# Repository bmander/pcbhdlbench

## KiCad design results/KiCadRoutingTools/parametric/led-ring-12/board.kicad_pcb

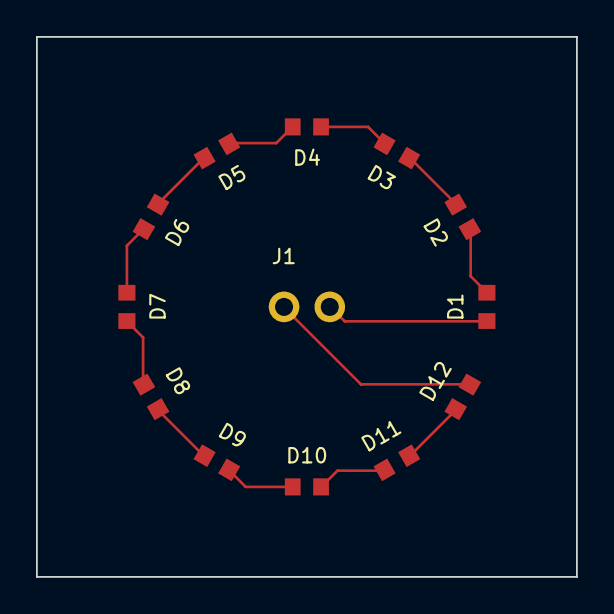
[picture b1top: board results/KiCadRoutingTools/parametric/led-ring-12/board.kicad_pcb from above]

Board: 2 copper layers, 30.0 x 30.0 mm, 13 parts (0 on the bottom side), 13 nets.

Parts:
D1, D2, D3, D4, D5, D6, D7, D8, D9, D10, D11, D12: LED_0603
J1: HDR_1x2_2.54

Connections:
GND: D1.K, J1.2
L1: D1.A, D2.K
L2: D2.A, D3.K
L3: D3.A, D4.K
L4: D4.A, D5.K
L5: D5.A, D6.K
L6: D6.A, D7.K
L7: D7.A, D8.K
L8: D8.A, D9.K
L9: D9.A, D10.K
L10: D10.A, D11.K
L11: D11.A, D12.K
VIN: D12.A, J1.1

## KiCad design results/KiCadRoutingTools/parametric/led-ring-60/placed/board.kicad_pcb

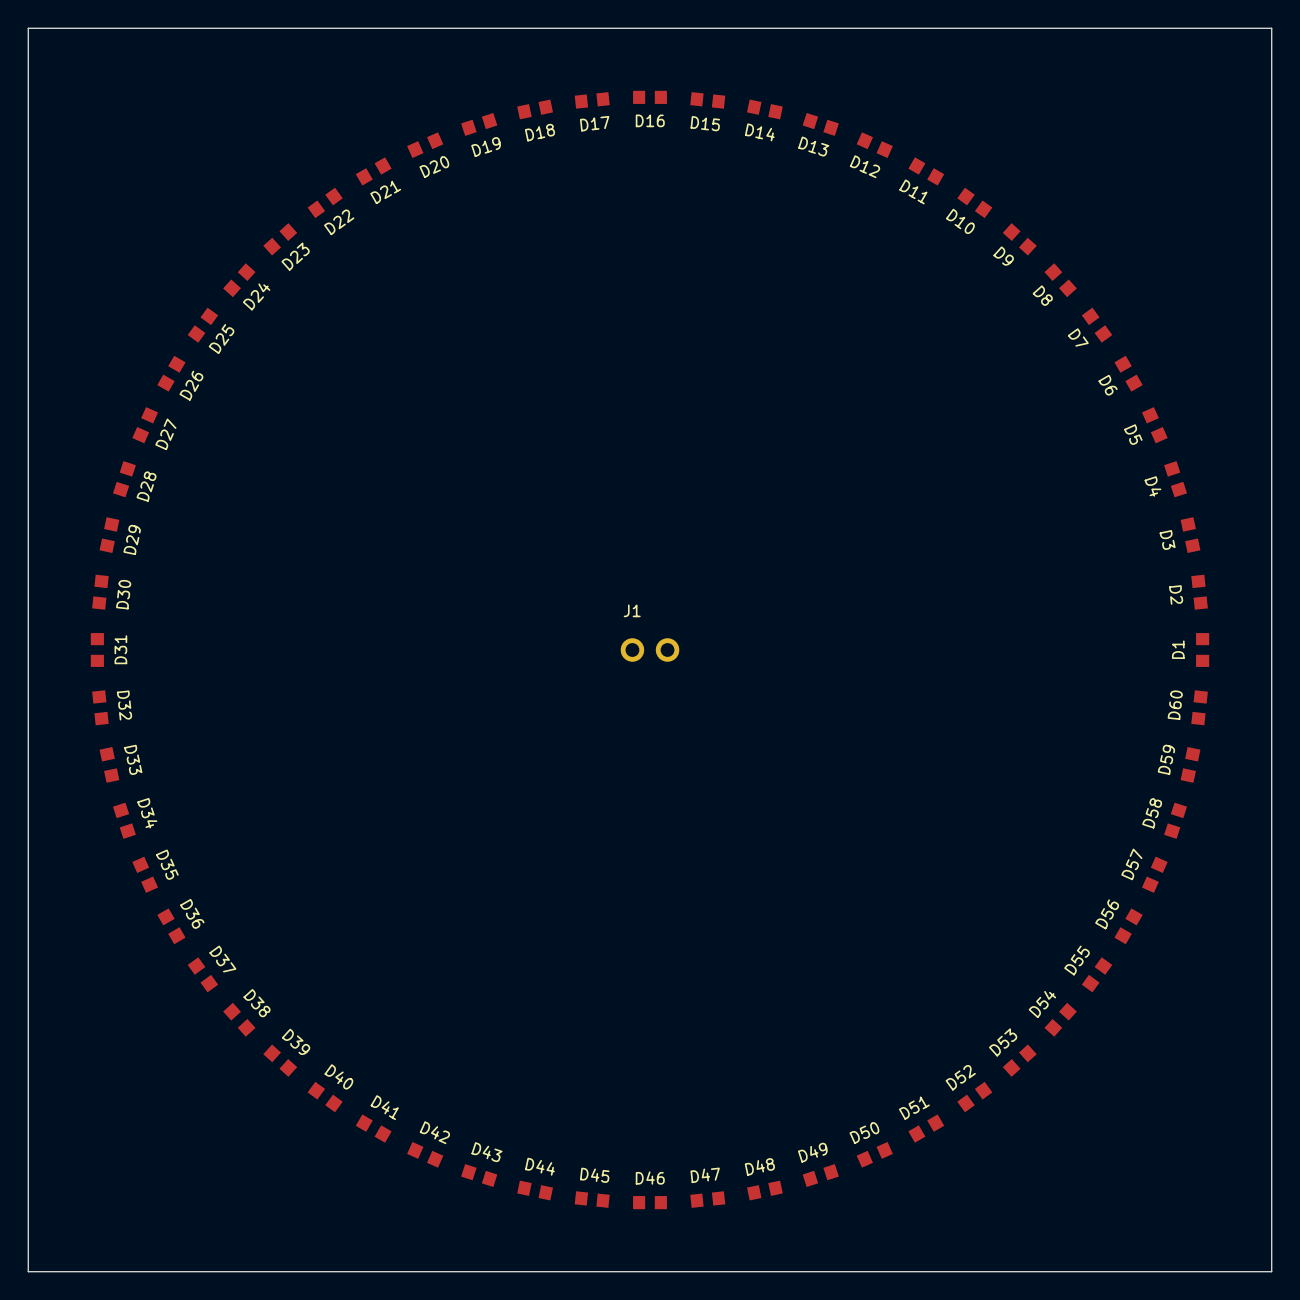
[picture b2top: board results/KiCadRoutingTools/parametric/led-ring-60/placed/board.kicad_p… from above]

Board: 2 copper layers, 90.0 x 90.0 mm, 61 parts (0 on the bottom side), 61 nets, no tracks yet.

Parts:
D1, D2, D3, D4, D5, D6, D7, D8, D9, D10, D11, D12, D13, D14, D15, D16, D17, D18, D19, D20, D21, D22, D23, D24, D25, D26, D27, D28, D29, D30, D31, D32, D33, D34, D35, D36, D37, D38, D39, D40, D41, D42, D43, D44, D45, D46, D47, D48, D49, D50, D51, D52, D53, D54, D55, D56, D57, D58, D59, D60: LED_0603
J1: HDR_1x2_2.54

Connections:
GND: D1.K, J1.2
L1: D1.A, D2.K
L2: D2.A, D3.K
L3: D3.A, D4.K
L4: D4.A, D5.K
L5: D5.A, D6.K
L6: D6.A, D7.K
L7: D7.A, D8.K
L8: D8.A, D9.K
L9: D9.A, D10.K
L10: D10.A, D11.K
L11: D11.A, D12.K
L12: D12.A, D13.K
L13: D13.A, D14.K
L14: D14.A, D15.K
L15: D15.A, D16.K
L16: D16.A, D17.K
L17: D17.A, D18.K
L18: D18.A, D19.K
L19: D19.A, D20.K
L20: D20.A, D21.K
L21: D21.A, D22.K
L22: D22.A, D23.K
L23: D23.A, D24.K
L24: D24.A, D25.K
L25: D25.A, D26.K
L26: D26.A, D27.K
L27: D27.A, D28.K
L28: D28.A, D29.K
L29: D29.A, D30.K
L30: D30.A, D31.K
L31: D31.A, D32.K
L32: D32.A, D33.K
L33: D33.A, D34.K
L34: D34.A, D35.K
L35: D35.A, D36.K
L36: D36.A, D37.K
L37: D37.A, D38.K
L38: D38.A, D39.K
L39: D39.A, D40.K
L40: D40.A, D41.K
L41: D41.A, D42.K
L42: D42.A, D43.K
L43: D43.A, D44.K
L44: D44.A, D45.K
L45: D45.A, D46.K
L46: D46.A, D47.K
L47: D47.A, D48.K
L48: D48.A, D49.K
L49: D49.A, D50.K
L50: D50.A, D51.K
L51: D51.A, D52.K
L52: D52.A, D53.K
L53: D53.A, D54.K
L54: D54.A, D55.K
L55: D55.A, D56.K
L56: D56.A, D57.K
L57: D57.A, D58.K
L58: D58.A, D59.K
L59: D59.A, D60.K
VIN: D60.A, J1.1

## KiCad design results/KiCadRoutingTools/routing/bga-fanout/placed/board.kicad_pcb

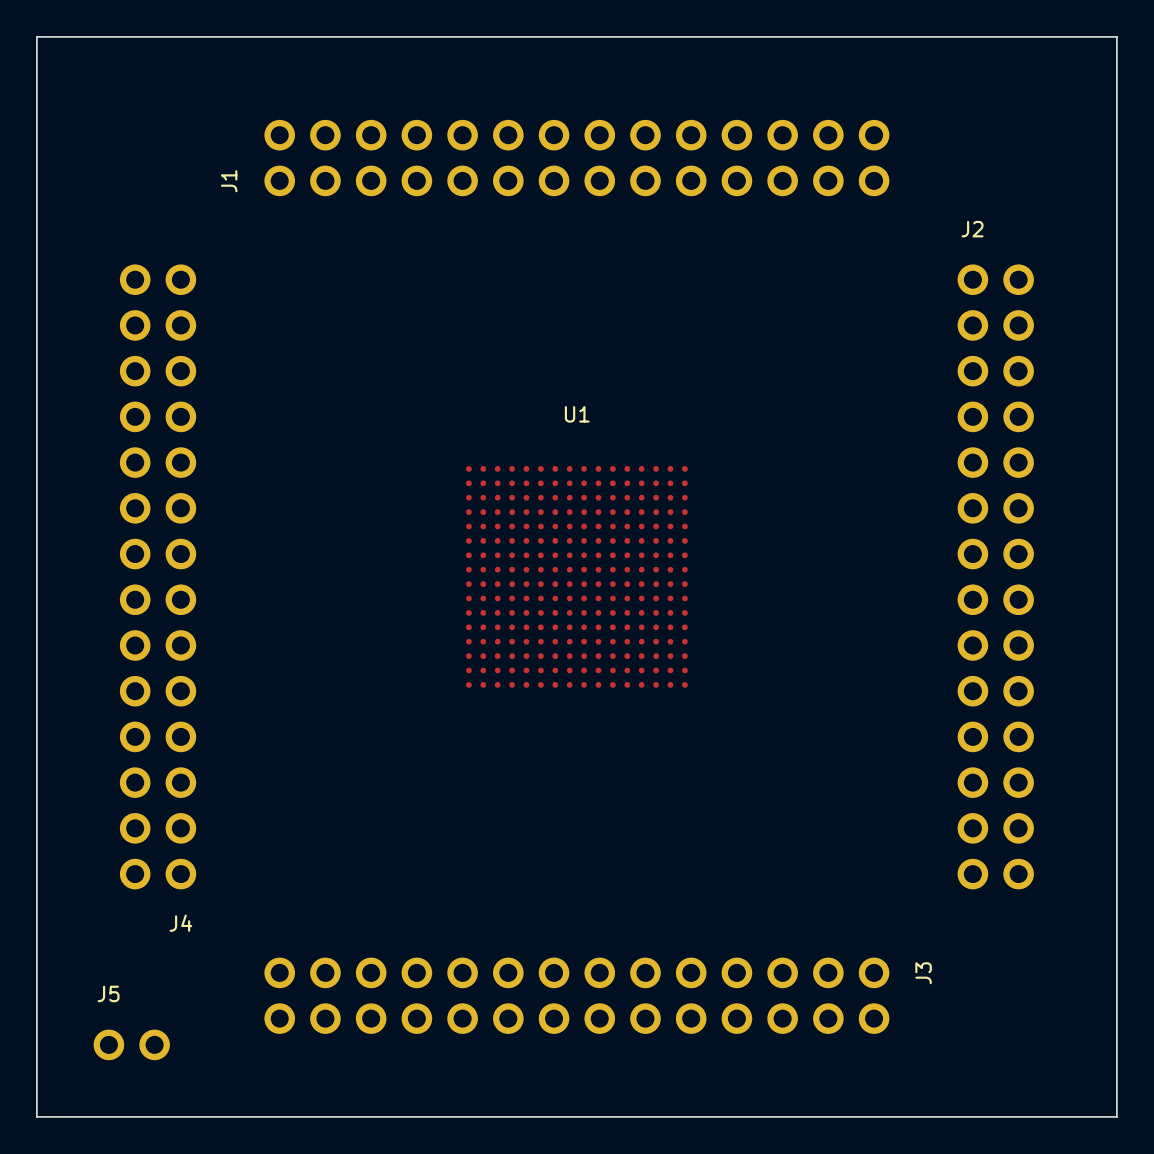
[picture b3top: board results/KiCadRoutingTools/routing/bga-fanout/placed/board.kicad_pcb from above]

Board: 4 copper layers, 60.0 x 60.0 mm, 6 parts (0 on the bottom side), 114 nets, no tracks yet.

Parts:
J1, J2, J3, J4: HDR_2x14_2.54
J5: HDR_1x2_2.54
U1: BGA-256

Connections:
A1: J1.1, U1.A1
A2: J1.2, U1.A2
A3: J1.4, U1.A3
A4: J1.6, U1.A4
A5: J1.8, U1.A5
A6: J1.10, U1.A6
A7: J1.12, U1.A7
A8: J1.14, U1.A8
A9: J1.16, U1.A9
A10: J1.18, U1.A10
A11: J1.20, U1.A11
A12: J1.22, U1.A12
A13: J1.24, U1.A13
A14: J1.26, U1.A14
A15: J1.28, U1.A15
A16: J2.1, U1.A16
B1: J4.28, U1.B1
B2: J1.3, U1.B2
B3: J1.5, U1.B3
B4: J1.7, U1.B4
B5: J1.9, U1.B5
B6: J1.11, U1.B6
B7: J1.13, U1.B7
B8: J1.15, U1.B8
B9: J1.17, U1.B9
B10: J1.19, U1.B10
B11: J1.21, U1.B11
B12: J1.23, U1.B12
B13: J1.25, U1.B13
B14: J1.27, U1.B14
B15: J2.3, U1.B15
B16: J2.2, U1.B16
C1: J4.26, U1.C1
C2: J4.27, U1.C2
C15: J2.5, U1.C15
C16: J2.4, U1.C16
D1: J4.24, U1.D1
D2: J4.25, U1.D2
D15: J2.7, U1.D15
D16: J2.6, U1.D16
E1: J4.22, U1.E1
E2: J4.23, U1.E2
E15: J2.9, U1.E15
E16: J2.8, U1.E16
F1: J4.20, U1.F1
F2: J4.21, U1.F2
F15: J2.11, U1.F15
F16: J2.10, U1.F16
G1: J4.18, U1.G1
G2: J4.19, U1.G2
G15: J2.13, U1.G15
G16: J2.12, U1.G16
GND: J5.2, U1.C3, U1.C5, U1.C7, U1.C9, U1.C11, U1.C13, U1.D4, U1.D6, U1.D8, U1.D10, U1.D12, U1.D14, U1.E3, U1.E5, U1.E7, U1.E9, U1.E11, U1.E13, U1.F4, U1.F6, U1.F8, U1.F10, U1.F12, U1.F14, U1.G3, U1.G5, U1.G7, U1.G9, U1.G11, U1.G13, U1.H4, U1.H6, U1.H8, U1.H10, U1.H12, U1.H14, U1.J3, U1.J5, U1.J7, U1.J9, U1.J11, U1.J13, U1.K4, U1.K6, U1.K8, U1.K10, U1.K12, U1.K14, U1.L3, U1.L5, U1.L7, U1.L9, U1.L11, U1.L13, U1.M4, U1.M6, U1.M8, U1.M10, U1.M12, U1.M14, U1.N3, U1.N5, U1.N7, U1.N9, U1.N11, U1.N13, U1.P4, U1.P6, U1.P8, U1.P10, U1.P12, U1.P14
H1: J4.16, U1.H1
H2: J4.17, U1.H2
H15: J2.15, U1.H15
H16: J2.14, U1.H16
J1: J4.14, U1.J1
J2: J4.15, U1.J2
J15: J2.17, U1.J15
J16: J2.16, U1.J16
K1: J4.12, U1.K1
K2: J4.13, U1.K2
K15: J2.19, U1.K15
K16: J2.18, U1.K16
L1: J4.10, U1.L1
L2: J4.11, U1.L2
L15: J2.21, U1.L15
L16: J2.20, U1.L16
M1: J4.8, U1.M1
M2: J4.9, U1.M2
M15: J2.23, U1.M15
M16: J2.22, U1.M16
N1: J4.6, U1.N1
N2: J4.7, U1.N2
N15: J2.25, U1.N15
N16: J2.24, U1.N16
P1: J4.4, U1.P1
P2: J4.5, U1.P2
P15: J2.27, U1.P15
P16: J2.26, U1.P16
R1: J4.2, U1.R1
R2: J4.3, U1.R2
R3: J3.27, U1.R3
R4: J3.25, U1.R4
R5: J3.23, U1.R5
R6: J3.21, U1.R6
R7: J3.19, U1.R7
R8: J3.17, U1.R8
R9: J3.15, U1.R9
R10: J3.13, U1.R10
R11: J3.11, U1.R11
R12: J3.9, U1.R12
R13: J3.7, U1.R13
R14: J3.5, U1.R14
R15: J3.3, U1.R15
R16: J2.28, U1.R16
T1: J4.1, U1.T1
T2: J3.28, U1.T2
T3: J3.26, U1.T3
T4: J3.24, U1.T4
T5: J3.22, U1.T5
T6: J3.20, U1.T6
T7: J3.18, U1.T7
T8: J3.16, U1.T8
T9: J3.14, U1.T9
T10: J3.12, U1.T10
T11: J3.10, U1.T11
T12: J3.8, U1.T12
T13: J3.6, U1.T13
T14: J3.4, U1.T14
T15: J3.2, U1.T15
T16: J3.1, U1.T16
VCC: J5.1, U1.C4, U1.C6, U1.C8, U1.C10, U1.C12, U1.C14, U1.D3, U1.D5, U1.D7, U1.D9, U1.D11, U1.D13, U1.E4, U1.E6, U1.E8, U1.E10, U1.E12, U1.E14, U1.F3, U1.F5, U1.F7, U1.F9, U1.F11, U1.F13, U1.G4, U1.G6, U1.G8, U1.G10, U1.G12, U1.G14, U1.H3, U1.H5, U1.H7, U1.H9, U1.H11, U1.H13, U1.J4, U1.J6, U1.J8, U1.J10, U1.J12, U1.J14, U1.K3, U1.K5, U1.K7, U1.K9, U1.K11, U1.K13, U1.L4, U1.L6, U1.L8, U1.L10, U1.L12, U1.L14, U1.M3, U1.M5, U1.M7, U1.M9, U1.M11, U1.M13, U1.N4, U1.N6, U1.N8, U1.N10, U1.N12, U1.N14, U1.P3, U1.P5, U1.P7, U1.P9, U1.P11, U1.P13
